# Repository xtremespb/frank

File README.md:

# FRANK

FRANK is a versatile hardware emulation platform based on Raspberry Pico and Raspberry Zero. It is a hardware fork of the [Murmulator](https://murmulator.ru/) project by [Alex Ekb](https://t.me/Alex_Eburg), incorporating numerous additional features.

The name "FRANK" is derived from "Frankenstein" as it integrates various components from different projects, similar to how Dr. Frankenstein created his monster from different parts. This combination enables FRANK to offer a unique and powerful set of capabilities.

## Supported Platforms

FRANK supports emulation for a variety of platforms, including:

* ZX Spectrum (48K, 128K and other models, including clones)
* IBM PC XT 8088
* BK-0011М (soviet 8 bit home computer)
* Radio 86RK (soviet 8 bit home computer)
* Atari 800
* NES/Famicom (also known as Dendy)
* Sega Master System
* Sega Game Gear
* NEC PC Engine / TurboGrafx 16
* Sega MegaDrive / Genesis
* Nintendo GameBoy
* Nintendo GameBoy Color
* Watara Supervision
* Atari Lynx
* Bandai Wonderswan
* NeoGeo Pocket Color
* Picomite MMBasic
* VersaTerm
* DOOM
* Macintosh 512K
* MurmulatorOS

## FRANK Models

Currently there are the following versions of FRANK available:

* [FRANK M1](./hardware/frank_m1) (latest hardware revision: 1.14)
* [FRANK M2](./hardware/frank_m2) (latest hardware revision: 1.02)
* [MiniFRANK RM1](./hardware/minifrank_rm1) (latest hardware revision: 2.01)
* [TurboFRANK](./hardware/turbofrank) (latest hardware revision: 1.02)

## Side Projects

* [HDMI2VGA](./hardware/hdmi2vga) - HDMI to VGA/Soft Composite passive adaptor (latest hardware revision: 2.01)
* [USB2PS2](./hardware/usb2ps2) - USB to PS/2 adapter built on RP2040-Zero (latest hardware revision: 1.03)
* [Protea](./hardware/protea) - hardware fork of [VersaTerm](https://github.com/dhansel/VersaTerm) DIY terminal built on plain RP2040 chip (latest hardware revision: 2.03)

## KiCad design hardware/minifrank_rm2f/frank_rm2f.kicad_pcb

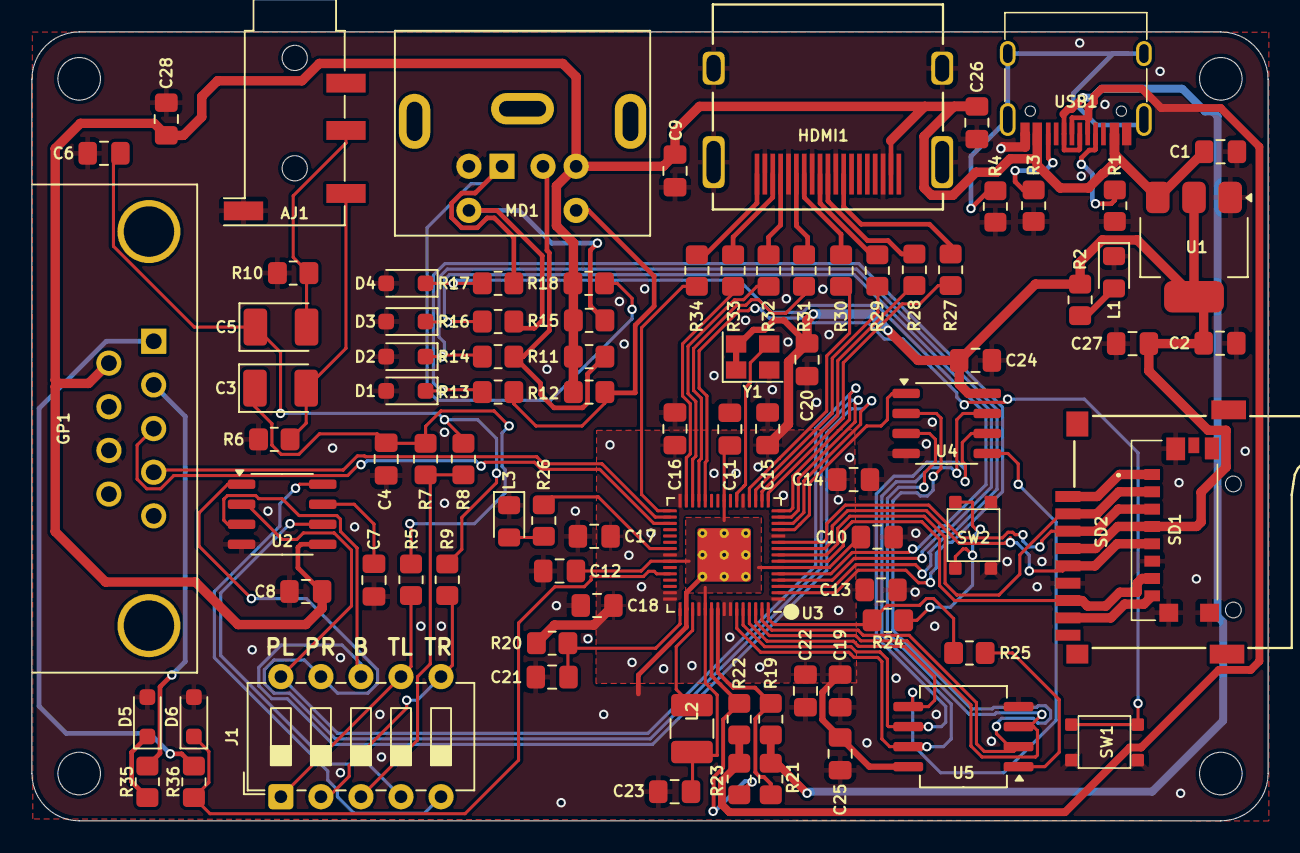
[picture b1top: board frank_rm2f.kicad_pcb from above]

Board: 2 copper layers, 78.4 x 50.0 mm, 93 parts (0 on the bottom side), 76 nets.

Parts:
AJ1: SJ1-353XNG; Jack (3.5mm, PJ-320D)
C1, C2, C9: 10u; Capacitor (0805)
C3, C5: 10u; Capacitor (3528, tantalum, polar)
C4, C6: 10n; Capacitor (0805)
C7: 1u; Capacitor (0805)
C8: 47u; Capacitor (0805)
C10, C12, C13, C14, C15, C16, C17, C18, C19, C20, C24, C25, C26, C27, C28: 100n; Capacitor (0805)
C11, C21, C22, C23: 4.7u; Capacitor (0805)
D1, D2, D3, D4, D5, D6: 3V3; Diode (SOD-323)
GP1: Gamepad; D-SUB (9 pin, male, top mount)
H1, H2, H3, H4: MountingHole; Mounting Hole (2.7mm)
HDMI1: HDMI Female; HDMI (female)
J1: Pin Header 2x18; DIP Switch (5x5)
L1: Green; LED (0805)
L2: 3.3u; Inductor (3225)
L3: Blue; LED (0805)
MD1: Mini-DIN-6; MiniDIN (6 Pin, female)
R1, R3: 5.1K; Resistor (0805)
R2, R5, R9, R11, R12, R15, R24, R26, R35, R36: 1K; Resistor (0805)
R4: 1M; Resistor (0805)
R6, R10: 330R; Resistor (0805)
R7, R8: 2K; Resistor (0805)
R13, R14, R16, R17: 100R; Resistor (0805)
R18: 1k; Resistor (0805)
R19, R22: 150R; Resistor (0805)
R20: 33; Resistor (0805)
R21, R23: 33R; Resistor (0805)
R25: 0; Resistor (0805)
R27, R28, R29, R30, R31, R32, R33, R34: 270R; Resistor (0805)
SD1: 47571-0001; MicroSD (SMD, short)
SD2: 104031-0811; MicroSD (SMD, long)
SW1: Reset; Button (SMD, 3x3mm, 1-1)
SW2: SW_Push; Button (SMD, 3x3mm, 1-1)
U1: NCP1117 3.3; SOT-223
U2: TDA1387T; SO-8
U3: RP2350_60QFN; QFN 60 (RP2350A)
U4: ESP-PSRAM32; SO-8
U5: W25Q128JVS; SOIC-8
USB1: USB4215-03-A; USB Type C
Y1: ASE-xxxMHz; Crystal (3225, active)

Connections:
+1V1: C10.1, C11.1, C12.1, C23.1, L2.1, U3.6 (DVDD), U3.23 (DVDD), U3.39 (DVDD), U3.50 (VREG_FB)
+3V3: C2.1, C13.1, C14.1, C15.1, C16.1, C17.1, C18.1, C19.1, C20.1, C22.1, C24.1, C25.1, C27.2, R2.2, R20.1, SD1.P4 (VDD), SD2.4 (VDD), U1.2 (VO), U3.1 (IOVDD), U3.11 (IOVDD), U3.20 (IOVDD), U3.30 (IOVDD), U3.38 (IOVDD), U3.44 (ADC_AVDD), U3.45 (IOVDD), U3.49 (VREG_VIN), U3.53 (USB_OTP_VDD), U3.54 (QSPI_IOVDD), U4.8 (VCC), U5.8 (VCC), Y1.1 (EN), Y1.4 (Vdd)
/A_OUTB: J1.5, R7.2, R8.2
/A_OUTL: J1.1, J1.8, R5.2
/A_OUTR: J1.3, J1.10, R9.2
/A_TDAL: J1.7, U2.6 (A_LEFT)
/A_TDAR: J1.9, U2.8 (A_RIGHT)
/Audio Out/L: AJ1.T, C3.2, R6.1
/Audio Out/R: AJ1.R, C5.2, R10.1
/D+: R19.1, R21.1, USB1.6 (DP1), USB1.8 (DP2)
/D-: R22.1, R23.1, USB1.5 (DN2), USB1.7 (DN1)
/GPIO0: D1.1 (K), R13.2, U3.2 (GPIO0)
/GPIO1: D2.1 (K), R14.2, U3.3 (GPIO1)
/GPIO2: D3.1 (K), R16.2, U3.4 (GPIO2)
/GPIO3: D4.1 (K), R17.2, U3.5 (GPIO3)
/GPIO4: SD1.P7 (DAT0), SD2.7 (DAT0), U3.7 (GPIO4)
/GPIO5: SD1.P2 (CD/DAT3), SD2.2 (DAT3/CD), U3.8 (GPIO5)
/GPIO6: SD1.P5 (CLK), SD2.5 (CLK), U3.9 (GPIO6)
/GPIO7: SD1.P3 (CMD), SD2.3 (CMD), U3.10 (GPIO7)
/GPIO8: U3.12 (GPIO8), U4.1 (~CE)
/GPIO9: J1.6, U2.3 (DATA), U3.13 (GPIO9)
/GPIO10: J1.4, U2.1 (SCLK), U3.14 (GPIO10)
/GPIO11: J1.2, U2.2 (LRCK), U3.15 (GPIO11)
/GPIO12: R27.2, U3.16 (GPIO12)
/GPIO13: R28.2, U3.17 (GPIO13)
/GPIO14: R29.2, U3.18 (GPIO14)
/GPIO15: R30.2, U3.19 (GPIO15)
/GPIO16: R31.2, U3.27 (GPIO16)
/GPIO17: R32.2, U3.28 (GPIO17)
/GPIO18: R33.2, U3.29 (GPIO18)
/GPIO19: R34.2, U3.31 (GPIO19)
/GPIO20: GP1.4, U3.32 (GPIO20)
/GPIO21: GP1.3, U3.33 (GPIO21)
/GPIO26: D5.1 (K), R35.1
/GPIO27: D6.1 (K), R36.1, U3.41 (GPIO27_ADC1)
/Gamepad/J1_DATA: GP1.2, R35.2
/Gamepad/J2_DATA: GP1.1, R36.2
/PS2/PS/2 CLK: MD1.5, R15.2, R16.1
/PS2/PS/2 DATA: MD1.1, R17.1, R18.2
/RP2350A/FLASH_SS: R25.2, U5.1 (~CS)
/RP2350A/QSPI_SCLK: U3.56 (QSPI_SCLK), U4.6 (SCLK), U5.6 (CLK)
/RP2350A/QSPI_SD0: U3.57 (QSPI_SD0), U4.5 (SI/SIO), U5.5 (DI(IO0))
/RP2350A/QSPI_SD1: U3.59 (QSPI_SD1), U4.2 (SO/SIO), U5.2 (DO(IO1))
/RP2350A/QSPI_SD2: U3.58 (QSPI_SD2), U4.3 (SIO2), U5.3 (IO2)
/RP2350A/QSPI_SD3: U3.55 (QSPI_SD3), U4.7 (SIO3), U5.7 (IO3)
/RP2350A/QSPI_SS: R24.1, R25.1, U3.60 (QSPI_SS)
/RP2350A/VREG_AVDD: C21.1, R20.2, U3.46 (VREG_AVDD)
/RP2350A/VREG_LX: L2.2, U3.48 (VREG_LX)
/RP2350A/XIN: U3.21 (XIN), Y1.3 (OUT)
/RP2350A/~USB_BOOT: R24.2, SW2.2
/RUN: SW1.1, U3.26 (RUN)
/SD Card/DAT1: SD1.P8 (DAT1), SD2.8 (DAT1)
/SD Card/DAT2: SD1.P1 (DAT2), SD2.1 (DAT2)
GND: AJ1.S, C1.2, C2.2, C4.2, C6.2, C7.2, C8.1, C9.2, C10.2, C11.2, C12.2, C13.2, C14.2, C15.2, C16.2, C17.2, C18.2, C19.2, C20.2, C21.2, C22.2, C23.2, C24.2, C25.2, C26.2, C27.1, C28.2, D1.2 (A), D2.2 (A), D3.2 (A), D4.2 (A), D5.2 (A), D6.2 (A), GP1.8, HDMI1.2 (G_D2), HDMI1.5 (G_D1), HDMI1.8 (G_D0), HDMI1.11 (G_CLK), HDMI1.17 (G_DDC/CEC), HDMI1.20 (SHIELD1), HDMI1.21 (SHIELD2), HDMI1.22 (SHIELD3), HDMI1.23 (SHIELD4), L1.1 (K), L3.1 (K), MD1.3, R1.1, R3.1, R4.2, R6.2, R10.2, SD1.G1 (GND_1), SD1.G2 (GND_2), SD1.G3 (GND_3), SD1.P6 (VSS), SD2.6 (VSS), SW1.2, SW2.1, U1.1 (GND), U2.4 (AGND), U3.47 (VREG_PGND), U3.61 (GND), U4.4 (VSS), U5.4 (GND), USB1.1 (GND), USB1.12 (GND), Y1.2 (GND)
GPIO25: R26.2, U3.37 (GPIO25)
unnamed: C3.1, C4.1, R5.1, R7.1
unnamed: C5.1, C6.1, R8.1, R9.1
unnamed: HDMI1.12 (CLKN), R27.1
unnamed: HDMI1.10 (CLKP), R28.1
unnamed: HDMI1.9 (D0N), R29.1
unnamed: HDMI1.7 (D0P), R30.1
unnamed: HDMI1.6 (D1N), R31.1
unnamed: HDMI1.4 (D1P), R32.1
unnamed: HDMI1.3 (D2N), R33.1
unnamed: HDMI1.1 (D2P), R34.1
unnamed: L1.2 (A), R2.1
unnamed: L3.2 (A), R26.1
unnamed: MD1.2, R11.2, R14.1
unnamed: MD1.6, R12.2, R13.1
unnamed: C7.1, U2.7 (FLT)
unnamed: R22.2, R23.2, U3.51 (USB_DM)
unnamed: R19.2, R21.2, U3.52 (USB_DP)
unnamed: R1.2, USB1.4 (CC1)
unnamed: R3.2, USB1.10 (CC2)
unnamed: R4.1, USB1.13 (SHIELD)
VBUS: C1.1, C8.2, C9.1, C26.1, C28.1, GP1.6, HDMI1.18 (+5V), MD1.4, R11.1, R12.1, R15.1, R18.1, U1.3 (VI), U2.5 (VA), USB1.2 (VBUS), USB1.11 (VBUS)

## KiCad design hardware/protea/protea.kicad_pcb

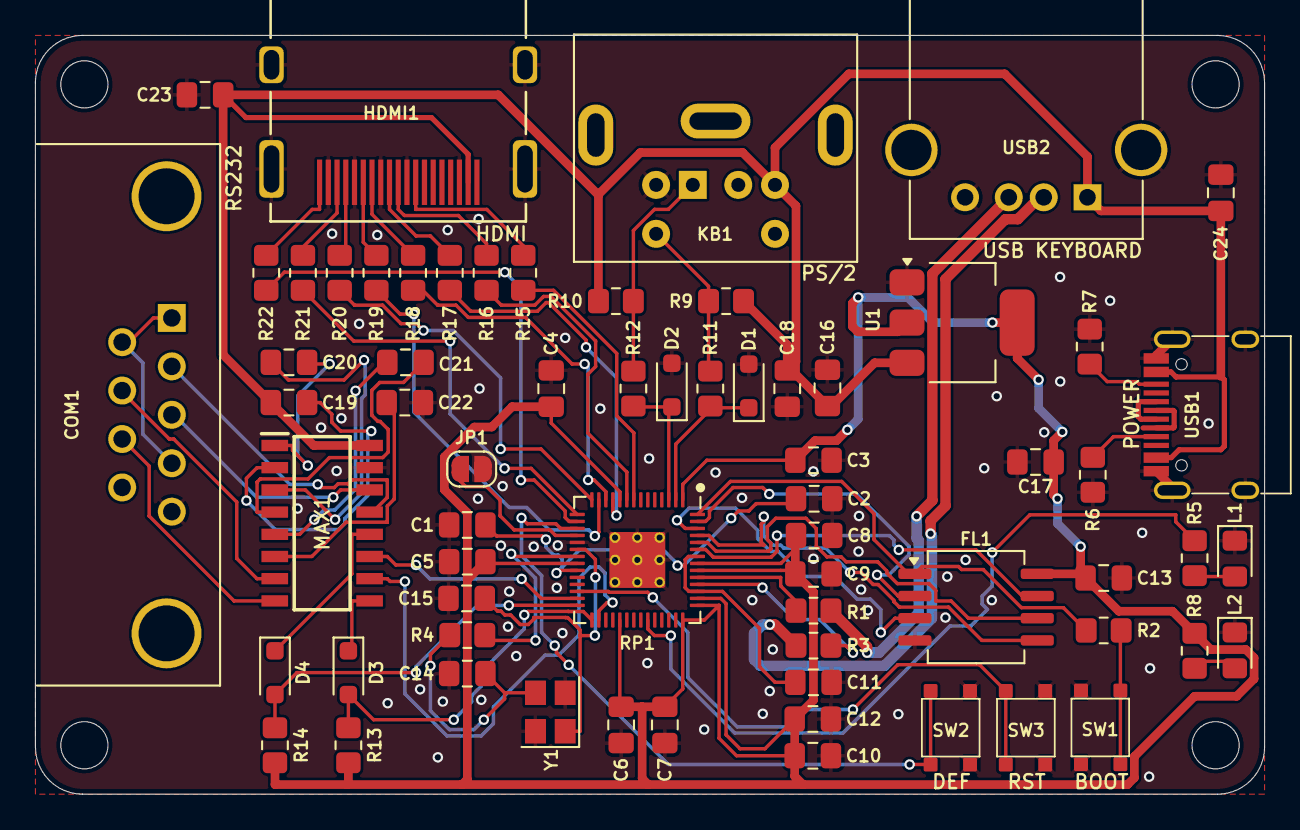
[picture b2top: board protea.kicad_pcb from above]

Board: 2 copper layers, 70.3 x 43.4 mm, 70 parts (0 on the bottom side), 65 nets.

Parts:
C1, C2, C3, C4, C5, C6, C7, C8, C9, C10, C13, C18, C23: 100n; Capacitor (0805)
C11, C12, C19, C20, C21, C22: 1u; Capacitor (0805)
C14, C15: 15p; Capacitor (0805)
C16, C17, C24: 10u; Capacitor (0805)
COM1: D-SUB 9 Male; D-SUB (9 pin, male, top mount)
D1, D2: 3V3; Diode (SOD-323)
D3, D4: 1N4148; Diode (SOD-323)
FL1: W25Q128JVSIQ; SOIC-8
H1, H2, H3, H4: MountingHole; MountingHole_2.7mm
HDMI1: DC3RX19JA2; HDMI (female)
JP1: HDMI_DEF; Jumper (solder)
KB1: PS/2; MiniDIN (6 Pin, female)
L1: Blue; LED (0805)
L2: Green; LED (0805)
MAX1: MAX232CSE+; SOIC127P600X175-16N
R1, R3: 27R; Resistor (0805)
R2, R4, R5, R8, R9, R13, R14: 1K; Resistor (0805)
R6, R7: 5.1K; Resistor (0805)
R10: 1k; Resistor (0805)
R11, R12: 100R; Resistor (0805)
R15, R16, R17, R18, R19, R20, R21, R22: 270R; Resistor (0805)
RP1: RP2040; QFN 56
SW1: Flash Button; Button (SMD, 3x3mm)
SW2, SW3: KLS7-TS3302; Button (SMD, 3x3mm)
U1: NCP1117 3.3; SOT-223
USB1: USB4215; USB Type C
USB2: 676430910; USB Type A (single)
Y1: 12 MHz; Crystal (3225)

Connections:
+3V3: C3.1, C4.1, C5.1, C6.1, C7.1, C8.1, C9.1, C10.1, C12.1, C13.1, C17.1, FL1.8 (VCC), R8.2, R13.2, R14.2, RP1.1 (IOVDD), RP1.10 (IOVDD), RP1.22 (IOVDD), RP1.33 (IOVDD), RP1.42 (IOVDD), RP1.43 (ADC_AVDD), RP1.44 (VREG_IN), RP1.48 (USB_VDD), RP1.49 (IOVDD), U1.2 (VO)
/GPIO0: D1.1 (K), R11.2, RP1.2 (GPIO0)
/GPIO1: D2.1 (K), R12.2, RP1.3 (GPIO1)
/GPIO6: R15.2, RP1.8 (GPIO6)
/GPIO7: R16.2, RP1.9 (GPIO7)
/GPIO8: R17.2, RP1.11 (GPIO8)
/GPIO9: R18.2, RP1.12 (GPIO9)
/GPIO10: R19.2, RP1.13 (GPIO10)
/GPIO11: R20.2, RP1.14 (GPIO11)
/GPIO12: R21.2, RP1.15 (GPIO12)
/GPIO13: R22.2, RP1.16 (GPIO13)
/GPIO14: RP1.17 (GPIO14), SW2.3, SW2.4
/GPIO15: JP1.1 (A), RP1.18 (GPIO15)
/GPIO16: MAX1.11 (T1IN), RP1.27 (GPIO16)
/GPIO17: D4.2 (A), R14.1, RP1.28 (GPIO17)
/GPIO18: D3.2 (A), R13.1, RP1.29 (GPIO18)
/GPIO19: MAX1.10 (T2IN), RP1.30 (GPIO19)
/PD+: USB1.6 (DP1), USB1.8 (DP2)
/PD-: USB1.5 (DN2), USB1.7 (DN1)
/RD+: R1.1, USB2.3 (D+)
/RD-: R3.1, USB2.2 (D-)
/RP2040/GPIO25: R5.2, RP1.37 (GPIO25)
/RP2040/QSPI_SCLK: FL1.6 (CLK), RP1.52 (QSPI_SCLK)
/RP2040/QSPI_SD0: FL1.5 (DI(IO0)), RP1.53 (QSPI_SD0)
/RP2040/QSPI_SD1: FL1.2 (DO(IO1)), RP1.55 (QSPI_SD1)
/RP2040/QSPI_SD2: FL1.3 (IO2), RP1.54 (QSPI_SD2)
/RP2040/QSPI_SD3: FL1.7 (IO3), RP1.51 (QSPI_SD3)
/RP2040/QSPI_SS: FL1.1 (~CS), R2.1, RP1.56 (QSPI_SS)
/RP2040/XIN: C15.1, RP1.20 (XIN), Y1.1
/RP2040/XOUT: R4.1, RP1.21 (XOUT)
/RP2040/~USB_BOOT: R2.2, SW1.3, SW1.4
/RS232/C1+: C20.2, MAX1.1 (C1+)
/RS232/C1-: C20.1, MAX1.3 (C1-)
/RS232/C2+: C21.2, MAX1.4 (C2+)
/RS232/C2-: C21.1, MAX1.5 (C2-)
/RS232/CTS_IN: COM1.7, MAX1.7 (T2OUT)
/RS232/CTS_MAX: D3.1 (K), MAX1.9 (R2OUT)
/RS232/RTS_IN: COM1.8, MAX1.8 (R2IN)
/RS232/RX_IN: COM1.3, MAX1.14 (T1OUT)
/RS232/RX_MAX: D4.1 (K), MAX1.12 (R1OUT)
/RS232/TX_IN: COM1.2, MAX1.13 (R1IN)
/RS232/V+: C19.1, MAX1.2 (V+)
/RS232/V-: C22.1, MAX1.6 (V-)
/RUN: RP1.26 (RUN), SW3.3, SW3.4
GND: C1.2, C2.2, C3.2, C4.2, C5.2, C6.2, C7.2, C8.2, C9.2, C10.2, C11.2, C12.2, C13.2, C14.2, C15.2, C16.2, C17.2, C18.2, C22.2, C23.2, C24.1, COM1.5, D1.2 (A), D2.2 (A), FL1.4 (GND), HDMI1.2 (G_D2), HDMI1.5 (G_D1), HDMI1.8 (G_D0), HDMI1.11 (G_CLK), HDMI1.17 (G_DDC/CEC), HDMI1.20 (SHIELD1), HDMI1.21 (SHIELD2), HDMI1.22 (SHIELD3), HDMI1.23 (SHIELD4), JP1.2 (B), KB1.3, L1.1 (K), L2.1 (K), MAX1.15 (GND), R6.1, R7.1, RP1.19 (TESTEN), RP1.57 (GND), SW1.1, SW1.2, SW2.1, SW2.2, SW3.1, SW3.2, U1.1 (GND), USB1.1 (GND), USB1.12 (GND), USB1.13 (SHIELD), USB2.4 (GND), USB2.5 (Shield), Y1.2, Y1.4
unnamed: C14.1, R4.2, Y1.3
unnamed: COM1.1, COM1.4, COM1.6
unnamed: HDMI1.12 (CLKN), R15.1
unnamed: HDMI1.10 (CLKP), R16.1
unnamed: HDMI1.9 (D0N), R17.1
unnamed: HDMI1.7 (D0P), R18.1
unnamed: HDMI1.6 (D1N), R19.1
unnamed: HDMI1.4 (D1P), R20.1
unnamed: HDMI1.3 (D2N), R21.1
unnamed: HDMI1.1 (D2P), R22.1
unnamed: KB1.1, R10.2, R12.1
unnamed: KB1.5, R9.2, R11.1
unnamed: L1.2 (A), R5.1
unnamed: L2.2 (A), R8.1
unnamed: R3.2, RP1.46 (USB_DM)
unnamed: R1.2, RP1.47 (USB_DP)
unnamed: C1.1, C2.1, C11.1, RP1.23 (DVDD), RP1.45 (VREG_VOUT), RP1.50 (DVDD)
unnamed: R6.2, USB1.4 (CC1)
unnamed: R7.2, USB1.10 (CC2)
VBUS: C16.1, C18.1, C19.2, C23.1, C24.2, HDMI1.18 (+5V), KB1.4, MAX1.16 (VCC), R9.1, R10.1, U1.3 (VI), USB1.2 (VBUS), USB1.11 (VBUS), USB2.1 (VBUS)

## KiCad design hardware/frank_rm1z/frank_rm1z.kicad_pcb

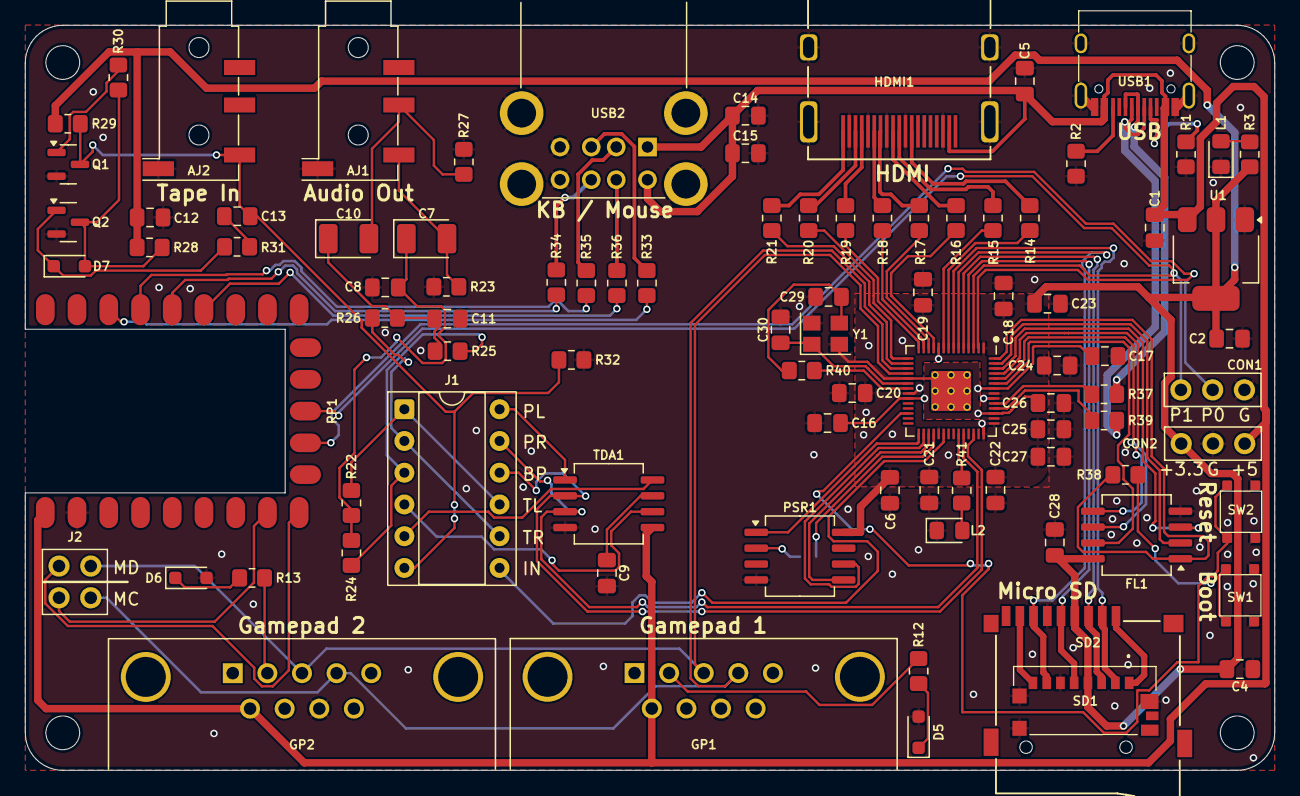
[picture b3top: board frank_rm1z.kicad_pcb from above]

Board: 2 copper layers, 100.0 x 59.6 mm, 96 parts (1 on the bottom side), 88 nets.

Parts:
AJ1, AJ2: PJ-320D; Jack (3.5mm, PJ-320D)
C1, C2, C9, C14, C15: 10u; Capacitor (0805)
C4, C5, C6, C12, C13, C16, C17, C18, C19, C20, C21, C22, C23, C24, C25, C28: 100n; Capacitor (0805)
C7, C10: 10u; Capacitor (3528, tantalum, polar)
C8, C11: 10n; Capacitor (0805)
C26, C27: 1u; Capacitor (0805)
C29, C30: 15p; Capacitor (0805)
CON1, CON2: Pin Header 1x03; Pin Header (1x03)
D5, D6: 3V3; Diode (SOD-323)
D7: 1N4148; Diode (SOD-323)
FL1: W25Q128JVSIQ; SOIC-8
GP1, GP2: D-SUB 9 Male; D-SUB (9 pin, male, top mount)
H1, H2, H3, H4: Hole 2.7mm; Mounting Hole (2.7mm)
HDMI1: DC3RX19JA2; HDMI (female)
J1: Pin Header 2x18; DIP Switch (6x6)
J2: Pin Header 2x18; Pin Header (2x02)
JP1: Jumper (Solder); Jumper (solder)
L1: Green; LED (0805)
L2: BLUE; LED (0805)
PSR1: ESP-PSRAM32; SOIC-8
Q1, Q2: BC850; SOT-23
R1, R2: 5.1K; Resistor (0805)
R3, R12, R13, R22, R26, R29, R38, R40, R41: 1K; Resistor (0805)
R14, R15, R16, R17, R18, R19, R20, R21: 270R; Resistor (0805)
R23, R27: 330R; Resistor (0805)
R24, R25: 2K; Resistor (0805)
R28, R30, R31: 10K; Resistor (0805)
R32: 100R; Resistor (0805)
R33, R34, R35, R36: 22R; Resistor (0805)
R37, R39: 27R; Resistor (0805)
RP1: RP2040-Zero; Raspberry Pi Zero (on board)
RP2: RP2040; QFN 56
SD1: 0475710001; MicroSD (SMD, short)
SD2: 104031-0811; MicroSD (SMD, long)
SW1, SW2: SW_Push; Button (SMD, 3x3mm, 1-1)
TDA1: TDA1387T; SOIC-8
U1: NCP1117 3.3; SOT-223
USB1: USB4215; USB Type C
USB2: SS-52100-004; USB Type A (stacked)
Y1: 12 MHz; Crystal (3225)

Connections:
+3V3: C2.1, C4.2, C6.1, C12.1, C18.1, C19.1, C20.1, C21.1, C22.1, C23.1, C24.1, C25.1, C27.1, C28.1, CON2.1, FL1.8 (VCC), PSR1.8 (VCC), R3.2, R28.1, R29.1, RP2.1 (IOVDD), RP2.10 (IOVDD), RP2.22 (IOVDD), RP2.33 (IOVDD), RP2.42 (IOVDD), RP2.43 (ADC_AVDD), RP2.44 (VREG_IN), RP2.48 (USB_VDD), RP2.49 (IOVDD), SD1.P4 (VDD), SD2.4 (VDD), U1.2 (VO)
/A_OUTB: J1.5, R24.2, R25.2
/A_OUTL: J1.1, J1.8, R22.2
/A_OUTR: J1.3, J1.10, R26.2
/A_TDAL: J1.7, TDA1.6 (A_LEFT)
/A_TDAR: J1.9, TDA1.8 (A_RIGHT)
/Audio Out/L: AJ1.T, C7.2, R23.1
/Audio Out/R: AJ1.R, C10.2, R27.1
/D+: R37.1, USB1.6 (DP1), USB1.8 (DP2)
/D-: R39.1, USB1.5 (DN2), USB1.7 (DN1)
/DAT1: SD1.P8 (DAT1), SD2.8 (DAT1)
/DAT2: SD1.P1 (DAT2), SD2.1 (DAT2)
/GP1_DATA: D5.1 (K), R12.1
/GP2_DATA: D6.1 (K), R13.1
/GPIO0: CON1.2, RP1.13 (12), RP2.2 (GPIO0)
/GPIO1: CON1.3, RP1.12 (11), RP2.3 (GPIO1)
/GPIO2: RP2.4 (GPIO2), SD1.P5 (CLK), SD2.5 (CLK)
/GPIO3: RP2.5 (GPIO3), SD1.P3 (CMD), SD2.3 (CMD)
/GPIO4: RP2.6 (GPIO4), SD1.P7 (DAT0), SD2.7 (DAT0)
/GPIO5: RP2.7 (GPIO5), SD1.P2 (CD/DAT3), SD2.2 (DAT3/CD)
/GPIO6: R14.2, RP2.8 (GPIO6)
/GPIO7: R15.2, RP2.9 (GPIO7)
/GPIO8: R16.2, RP2.11 (GPIO8)
/GPIO9: R17.2, RP2.12 (GPIO9)
/GPIO10: R18.2, RP2.13 (GPIO10)
/GPIO11: R19.2, RP2.14 (GPIO11)
/GPIO12: R20.2, RP2.15 (GPIO12)
/GPIO13: R21.2, RP2.16 (GPIO13)
/GPIO14: GP1.4, GP2.4, J2.4, RP2.17 (GPIO14)
/GPIO15: GP1.3, GP2.3, J2.2, RP2.18 (GPIO15)
/GPIO18: PSR1.1 (~CE), RP2.29 (GPIO18)
/GPIO19: PSR1.6 (SCLK), RP2.30 (GPIO19)
/GPIO20: PSR1.5 (SI/SIO), RP2.31 (GPIO20)
/GPIO21: JP1.2 (B), RP2.32 (GPIO21)
/GPIO22: J1.12, RP2.34 (GPIO22)
/GPIO26: J1.4, RP2.38 (GPIO26_ADC0), TDA1.3 (DATA)
/GPIO27: J1.2, TDA1.1 (SCLK)
/GPIO28: J1.6, RP2.40 (GPIO28_ADC2), TDA1.2 (LRCK)
/LOAD_IN_D: AJ2.T, C13.1, J1.11, Q1.3 (C), R29.2, R32.1
/MS_CLK: J2.3, RP1.16 (15)
/MS_DATA: J2.1, RP1.15 (14)
/RP2040/GPIO25: R41.2, RP2.37 (GPIO25)
/RP2040/QSPI_SCLK: FL1.6 (CLK), RP2.52 (QSPI_SCLK)
/RP2040/QSPI_SD0: FL1.5 (DI(IO0)), RP2.53 (QSPI_SD0)
/RP2040/QSPI_SD1: FL1.2 (DO(IO1)), RP2.55 (QSPI_SD1)
/RP2040/QSPI_SD2: FL1.3 (IO2), RP2.54 (QSPI_SD2)
/RP2040/QSPI_SD3: FL1.7 (IO3), RP2.51 (QSPI_SD3)
/RP2040/QSPI_SS: FL1.1 (~CS), R38.1, RP2.56 (QSPI_SS)
/RP2040/RUN: RP2.26 (RUN), SW2.1
/RP2040/XIN: C30.1, RP2.20 (XIN), Y1.1
/RP2040/XOUT: R40.1, RP2.21 (XOUT)
/RP2040/~USB_BOOT: R38.2, SW1.2
/USB_D1M: R35.1, RP1.4 (3)
/USB_D1P: R33.1, RP1.3 (2)
/USB_D2M: R36.1, RP1.6 (5)
/USB_D2P: R34.1, RP1.5 (4)
GND: AJ1.S, AJ2.S, C1.2, C2.2, C4.1, C5.2, C6.2, C8.2, C9.2, C11.2, C12.2, C14.2, C15.2, C16.2, C17.2, C18.2, C19.2, C20.2, C21.2, C22.2, C23.2, C24.2, C25.2, C26.2, C27.2, C28.2, C29.2, C30.2, CON1.1, CON2.2, D5.2 (A), D6.2 (A), FL1.4 (GND), GP1.8, GP2.8, HDMI1.2 (G_D2), HDMI1.5 (G_D1), HDMI1.8 (G_D0), HDMI1.11 (G_CLK), HDMI1.17 (G_DDC/CEC), HDMI1.20 (SHIELD1), HDMI1.21 (SHIELD2), HDMI1.22 (SHIELD3), HDMI1.23 (SHIELD4), L1.1 (K), L2.1 (K), PSR1.4 (VSS), Q1.2 (E), Q2.2 (E), R1.1, R2.1, R23.2, R27.2, R32.2, RP1.22 (GND), RP2.19 (TESTEN), RP2.57 (GND), SD1.G1 (GND_1), SD1.G2 (GND_2), SD1.G3 (GND_3), SD1.P6 (VSS), SD2.6 (VSS), SW1.1, SW2.2, TDA1.4 (AGND), U1.1 (GND), USB1.1 (GND), USB1.12 (GND), USB1.13 (SHIELD), USB2.4 (GND1), USB2.8 (GND2), USB2.9 (Shield), Y1.2, Y1.4
unnamed: C7.1, C8.1, R22.1, R24.1
unnamed: C10.1, C11.1, R25.1, R26.1
unnamed: C13.2, R31.1
unnamed: C29.1, R40.2, Y1.3
unnamed: D7.2 (A), Q2.3 (C), R28.2, R30.1
unnamed: D7.1 (K), Q2.1 (B), R31.2
unnamed: GP1.2, R12.2
unnamed: GP2.2, R13.2
unnamed: HDMI1.12 (CLKN), R14.1
unnamed: HDMI1.10 (CLKP), R15.1
unnamed: HDMI1.9 (D0N), R16.1
unnamed: HDMI1.7 (D0P), R17.1
unnamed: HDMI1.6 (D1N), R18.1
unnamed: HDMI1.4 (D1P), R19.1
unnamed: HDMI1.3 (D2N), R20.1
unnamed: HDMI1.1 (D2P), R21.1
unnamed: JP1.1 (A), PSR1.2 (SO/SIO)
unnamed: L1.2 (A), R3.1
unnamed: L2.2 (A), R41.1
unnamed: Q1.1 (B), R30.2
unnamed: R39.2, RP2.46 (USB_DM)
unnamed: R37.2, RP2.47 (USB_DP)
unnamed: C16.1, C17.1, C26.1, RP2.23 (DVDD), RP2.45 (VREG_VOUT), RP2.50 (DVDD)
unnamed: C9.1, TDA1.7 (FLT)
unnamed: R1.2, USB1.4 (CC1)
unnamed: R2.2, USB1.10 (CC2)
unnamed: R33.2, USB2.3 (D1+)
unnamed: R35.2, USB2.2 (D1-)
unnamed: R34.2, USB2.7 (D2+)
unnamed: R36.2, USB2.6 (D2-)
VBUS: C1.1, C5.1, C14.1, C15.1, CON2.3, GP1.6, GP2.6, HDMI1.18 (+5V), RP1.23 (5V), TDA1.5 (VA), U1.3 (VI), USB1.2 (VBUS), USB1.11 (VBUS), USB2.1 (VBUS1), USB2.5 (VBUS2)

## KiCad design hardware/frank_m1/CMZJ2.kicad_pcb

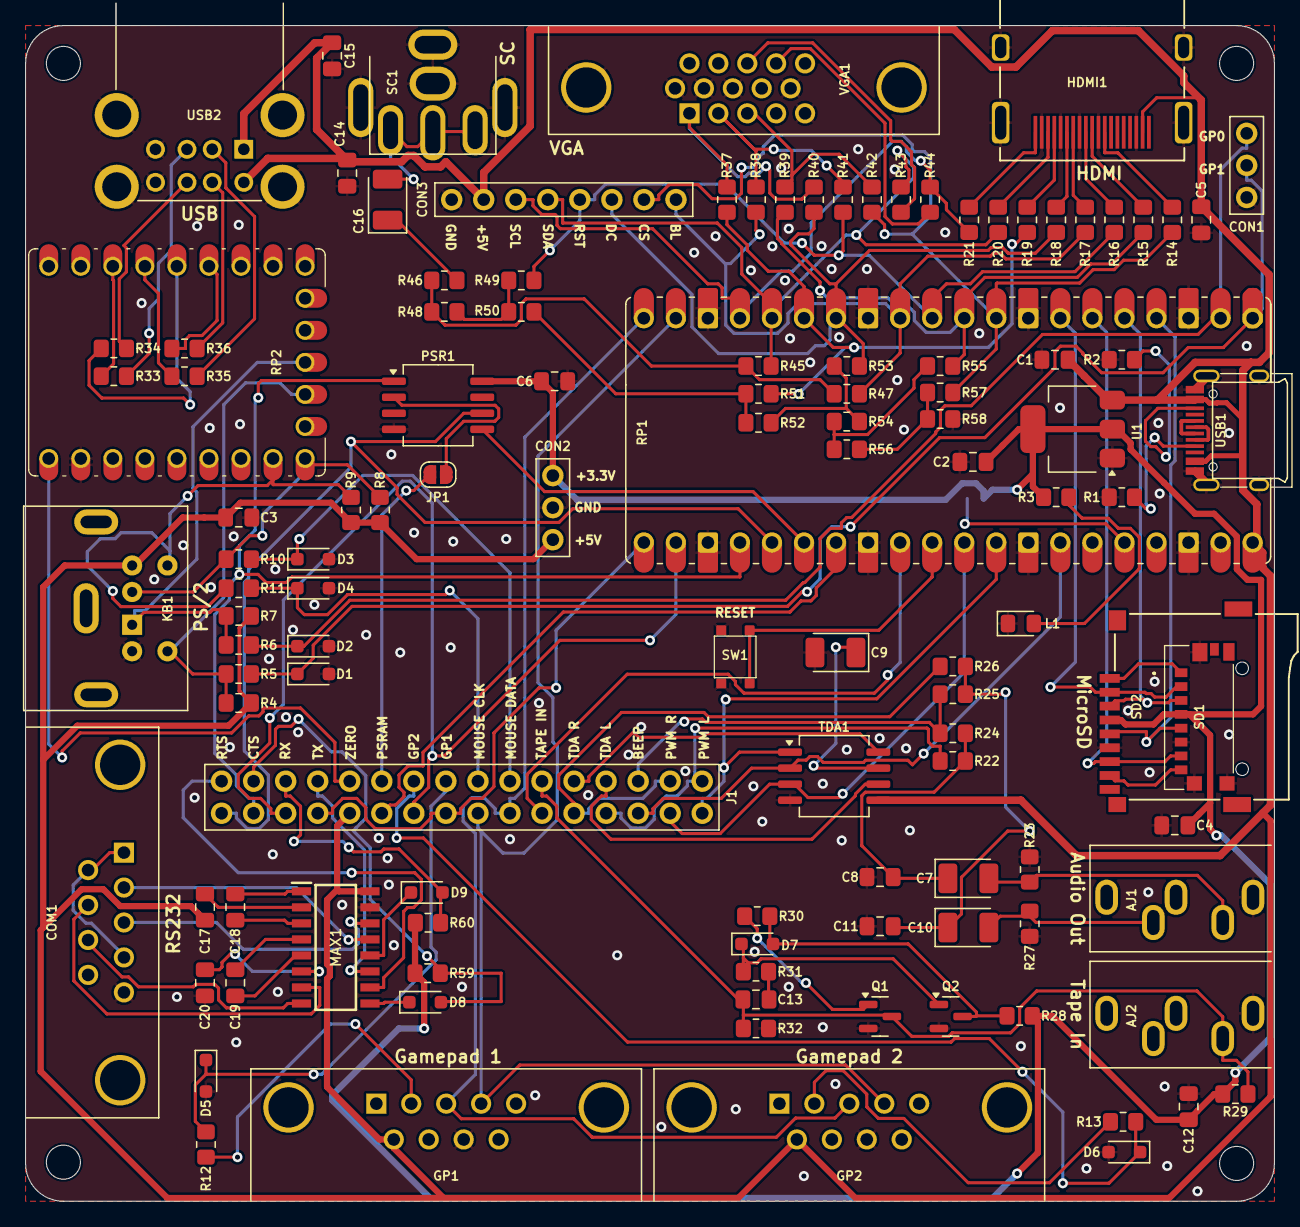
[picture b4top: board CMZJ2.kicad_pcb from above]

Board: 2 copper layers, 99.0 x 93.2 mm, 122 parts (1 on the bottom side), 112 nets.

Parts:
AJ1, AJ2: SJ1-353XNG; Jack (3.5mm)
C1, C2, C14, C15: 10u; Capacitor (0805)
C3, C4, C5, C6, C12, C13: 100n; Capacitor (0805)
C7, C9, C10: 10u; Capacitor (3528, tantalum, polar)
C8, C11: 10n; Capacitor (0805)
C16: 220u; Capacitor (3528, tantalum, polar)
C17, C18, C19, C20: 1u; Capacitor (0805)
COM1: D-SUB 9 Male; D-SUB (9 pin, male, top mount)
CON1, CON2: Pin Header 1x03; Pin Header (1x03)
CON3: Pin Header 1x08; Pin Header (1x08)
D1, D2, D3, D4, D5, D6: 3V3; Diode (SOD-323)
D7, D8, D9: 1N4148; Diode (SOD-323)
GP1, GP2: D-SUB 9 Male; D-SUB (9 pin, male, top mount)
H1, H2, H3, H4: Hole 2.7mm; Mounting Hole (2.7mm)
HDMI1: DC3RX19JA2; HDMI (female)
J1: Pin Header 2x18; Pin Header (2x16)
JP1, JP2: Jumper (Solder); Jumper (solder)
KB1: MDC-036; MiniDIN (6 Pin, female)
L1: Green; LED (0805)
MAX1: MAX232CSE+; SOIC127P600X175-16N
PSR1: ESP-PSRAM32; SOIC-8
Q1, Q2: BC850; SOT-23
R1, R2: 5.1K; Resistor (0805)
R3, R4, R7, R8, R9, R12, R13, R22, R26, R29, R40, R41, R42, R59, R60: 1K; Resistor (0805)
R5, R6, R10, R11, R32, R43, R44: 100R; Resistor (0805)
R14, R15, R16, R17, R18, R19, R20, R21, R47, R49, R51, R53, R55, R57: 270R; Resistor (0805)
R23, R27, R37, R38, R39: 330R; Resistor (0805)
R24, R25: 2K; Resistor (0805)
R28, R30, R31: 10K; Resistor (0805)
R33, R34, R35, R36: 22R; Resistor (0805)
R45: 750R; Resistor (0805)
R46: 51R; Resistor (0805)
R48, R50, R52, R54, R56: 150R; Resistor (0805)
R58: 300R; Resistor (0805)
RP1: Rasberry Pi Pico; Raspberry Pi Pico
RP2: RP2040-Zero; Raspberry Pi Zero
SC1: RCA-103; RCA
SD1: 0475710001; MicroSD (SMD, short)
SD2: 104031-0811; MicroSD (SMD, long)
SW1: KLS7-TS3302; Button (SMD, 3x3mm)
TDA1: TDA1387T; SOIC-8
U1: NCP1117 3.3; SOT-223
USB1: USB4215; USB Type C
USB2: SS-52100-004; USB Type A (stacked)
VGA1: D-SUB 15 Female; D-SUB (15 pin, female)

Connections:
+3V3: C2.1, C4.2, C6.1, C12.1, CON2.1, JP2.2 (B), PSR1.8 (VCC), R3.2, R28.1, R29.1, R59.2, R60.2, SD1.P4 (VDD), SD2.4 (VDD), U1.2 (VO)
/A_OUTB: J1.5, R24.2, R25.2
/A_OUTL: J1.1, J1.8, R22.2
/A_OUTR: J1.3, J1.10, R26.2
/A_TDAL: J1.7, TDA1.6 (A_LEFT)
/A_TDAR: J1.9, TDA1.8 (A_RIGHT)
/Audio Out/L: AJ1.T, C7.2, R23.1
/Audio Out/R: AJ1.R, C10.2, R27.1
/Composite/CVBS: C16.2, SC1.1
/GP1_DATA: D5.1 (K), J1.17, R12.1
/GP2_DATA: D6.1 (K), J1.19, R13.1
/GPIO0: CON1.2, D1.1 (K), R5.2, RP1.1 (GPIO0)
/GPIO1: CON1.3, D2.1 (K), R6.2, RP1.2 (GPIO1)
/GPIO2: RP1.4 (GPIO2), SD1.P5 (CLK), SD2.5 (CLK)
/GPIO3: RP1.5 (GPIO3), SD1.P3 (CMD), SD2.3 (CMD)
/GPIO4: RP1.6 (GPIO4), SD1.P7 (DAT0), SD2.7 (DAT0)
/GPIO5: RP1.7 (GPIO5), SD1.P2 (CD/DAT3), SD2.2 (DAT3/CD)
/GPIO6: CON3.7, R14.2, R42.1, R57.1, RP1.9 (GPIO6)
/GPIO7: R15.2, R39.1, R55.1, RP1.10 (GPIO7)
/GPIO8: CON3.5, R16.2, R41.1, R49.1, RP1.11 (GPIO8)
/GPIO9: CON3.8, R17.2, R38.1, R47.1, RP1.12 (GPIO9)
/GPIO10: CON3.6, R18.2, R40.1, R53.1, RP1.14 (GPIO10)
/GPIO11: R19.2, R37.1, R51.1, RP1.15 (GPIO11)
/GPIO12: CON3.4, R20.2, R43.2, R45.1, RP1.16 (GPIO12)
/GPIO13: CON3.3, R21.2, R44.2, RP1.17 (GPIO13)
/GPIO14: GP1.4, GP2.4, J1.16, RP1.19 (GPIO14)
/GPIO15: GP1.3, GP2.3, J1.14, RP1.20 (GPIO15)
/GPIO16: J1.18, J1.26, RP1.21 (GPIO16)
/GPIO17: J1.20, J1.28, RP1.22 (GPIO17)
/GPIO18: J1.30, PSR1.1 (~CE), RP1.24 (GPIO18)
/GPIO19: J1.32, PSR1.6 (SCLK), RP1.25 (GPIO19)
/GPIO20: PSR1.5 (SI/SIO), RP1.26 (GPIO20)
/GPIO21: J1.22, RP1.27 (GPIO21)
/GPIO22: J1.12, RP1.29 (GPIO22)
/GPIO26: J1.4, RP1.31 (GPIO26_ADC0), TDA1.3 (DATA)
/GPIO27: J1.2, RP1.32 (GPIO27_ADC1), TDA1.1 (SCLK)
/GPIO28: J1.6, RP1.34 (GPIO28_ADC2), TDA1.2 (LRCK)
/KB_CLK: KB1.5, R4.2, R5.1, RP2.13 (12)
/KB_DATA: KB1.1, R6.1, R7.2, RP2.12 (11)
/LOAD_IN_D: AJ2.T, C13.1, J1.11, Q1.3 (C), R29.2, R32.1
/MS_CLK: KB1.6, R9.2, R11.1, RP2.16 (15)
/MS_CLK_3V: D4.1 (K), J1.15, R11.2
/MS_DATA: KB1.2, R8.2, R10.1, RP2.15 (14)
/MS_DATA_3V: D3.1 (K), J1.13, R10.2
/Micro SD/DAT1: SD1.P8 (DAT1), SD2.8 (DAT1)
/Micro SD/DAT2: SD1.P1 (DAT2), SD2.1 (DAT2)
/PSR_SOSIO: J1.21, JP1.2 (B)
/Power/D+: USB1.6 (DP1), USB1.8 (DP2)
/Power/D-: USB1.5 (DN2), USB1.7 (DN1)
/RS232/C1+: C18.2, MAX1.1 (C1+)
/RS232/C1-: C18.1, MAX1.3 (C1-)
/RS232/C2+: C19.2, MAX1.4 (C2+)
/RS232/C2-: C19.1, MAX1.5 (C2-)
/RS232/CTS_IN: COM1.7, MAX1.7 (T2OUT)
/RS232/CTS_MAX: D8.1 (K), MAX1.9 (R2OUT)
/RS232/RTS_IN: COM1.8, MAX1.8 (R2IN)
/RS232/RX_IN: COM1.3, MAX1.14 (T1OUT)
/RS232/RX_MAX: D9.1 (K), MAX1.12 (R1OUT)
/RS232/TX_IN: COM1.2, MAX1.13 (R1IN)
/RS232/V+: C17.1, MAX1.2 (V+)
/RS232/V-: C20.1, MAX1.6 (V-)
/RS232_CTS: D8.2 (A), J1.29, R59.1
/RS232_RTS: J1.31, MAX1.10 (T2IN)
/RS232_RX: D9.2 (A), J1.27, R60.1
/RS232_TX: J1.25, MAX1.11 (T1IN)
/RUN: RP1.30 (RUN), SW1.3, SW1.4
/USB_D1M: R35.1, RP2.4 (3)
/USB_D1P: R33.1, RP2.3 (2)
/USB_D2M: R36.1, RP2.6 (5)
/USB_D2P: R34.1, RP2.5 (4)
/ZERO_VBUS: J1.23, RP2.23 (5V)
GND: AJ1.S, AJ2.S, C1.2, C2.2, C3.2, C4.1, C5.2, C6.2, C8.2, C9.2, C11.2, C12.2, C14.2, C15.2, C20.2, COM1.5, CON1.1, CON2.2, CON3.1, D1.2 (A), D2.2 (A), D3.2 (A), D4.2 (A), D5.2 (A), D6.2 (A), GP1.8, GP2.8, HDMI1.2 (G_D2), HDMI1.5 (G_D1), HDMI1.8 (G_D0), HDMI1.11 (G_CLK), HDMI1.17 (G_DDC/CEC), HDMI1.20 (SHIELD1), HDMI1.21 (SHIELD2), HDMI1.22 (SHIELD3), HDMI1.23 (SHIELD4), KB1.3, L1.1 (K), MAX1.15 (GND), PSR1.4 (VSS), Q1.2 (E), Q2.2 (E), R1.1, R2.1, R23.2, R27.2, R32.2, R58.1, RP1.3 (GND), RP1.8 (GND), RP1.13 (GND), RP1.18 (GND), RP1.23 (GND), RP1.28 (GND), RP1.33 (AGND), RP1.38 (GND), RP2.22 (GND), SC1.2, SD1.G1 (GND_1), SD1.G2 (GND_2), SD1.G3 (GND_3), SD1.P6 (VSS), SD2.6 (VSS), SW1.1, SW1.2, TDA1.4 (AGND), U1.1 (GND), USB1.1 (GND), USB1.12 (GND), USB1.13 (SHIELD), USB2.4 (GND1), USB2.8 (GND2), USB2.9 (Shield), VGA1.0, VGA1.5, VGA1.6, VGA1.7, VGA1.8, VGA1.10
unnamed: C7.1, C8.1, R22.1, R24.1
unnamed: C10.1, C11.1, R25.1, R26.1
unnamed: C13.2, R31.1
unnamed: C16.1, R46.2
unnamed: COM1.1, COM1.4, COM1.6
unnamed: D7.2 (A), Q2.3 (C), R28.2, R30.1
unnamed: D7.1 (K), Q2.1 (B), R31.2
unnamed: GP1.2, R12.2
unnamed: GP2.2, R13.2
unnamed: HDMI1.12 (CLKN), R14.1
unnamed: HDMI1.10 (CLKP), R15.1
unnamed: HDMI1.9 (D0N), R16.1
unnamed: HDMI1.7 (D0P), R17.1
unnamed: HDMI1.6 (D1N), R18.1
unnamed: HDMI1.4 (D1P), R19.1
unnamed: HDMI1.3 (D2N), R20.1
unnamed: HDMI1.1 (D2P), R21.1
unnamed: JP1.1 (A), PSR1.2 (SO/SIO)
unnamed: JP2.1 (A), RP1.36 (3V3)
unnamed: L1.2 (A), R3.1
unnamed: Q1.1 (B), R30.2
unnamed: R37.2, R40.2, VGA1.1
unnamed: R38.2, R41.2, VGA1.2
unnamed: R39.2, R42.2, VGA1.3
unnamed: R43.1, VGA1.13
unnamed: R44.1, VGA1.14
unnamed: R45.2, R46.1, R47.2, R48.2
unnamed: R48.1, R49.2, R50.2
unnamed: R50.1, R51.2, R52.2
unnamed: R52.1, R53.2, R54.2
unnamed: R54.1, R55.2, R56.2
unnamed: R56.1, R57.2, R58.2
unnamed: C9.1, TDA1.7 (FLT)
unnamed: R1.2, USB1.4 (CC1)
unnamed: R2.2, USB1.10 (CC2)
unnamed: R33.2, USB2.3 (D1+)
unnamed: R35.2, USB2.2 (D1-)
unnamed: R34.2, USB2.7 (D2+)
unnamed: R36.2, USB2.6 (D2-)
VBUS: C1.1, C3.1, C5.1, C14.1, C15.1, C17.2, CON2.3, CON3.2, GP1.6, GP2.6, HDMI1.18 (+5V), J1.24, KB1.4, MAX1.16 (VCC), R4.1, R7.1, R8.1, R9.1, RP1.40 (VBUS), TDA1.5 (VA), U1.3 (VI), USB1.2 (VBUS), USB1.11 (VBUS), USB2.1 (VBUS1), USB2.5 (VBUS2)
